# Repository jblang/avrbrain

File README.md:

# AVRBrain

AVRbrain is an [AVR128DB64](https://www.microchip.com/en-us/product/avr128db64) dev board.  The AVR Dx series are modern AVRs with many desireable features over the classic ATmega AVRs, such as multi-voltage I/O, configurable logic, advanced analog features, and a single-wire programming and debug interface.

## Arduino Compatibility

AVRbrain is compatible with the [DxCore](https://github.com/SpenceKonde/DxCore) Arduino Core. I have tested the AVR128DB28 on a breadboard with the same programming circuit I intend to use on the finished board, and confirmed that it works.

Once flashed in UPDI programming mode, the Optiboot_Dx bootloader can be used to reprogram the board in serial comms mode, and there is an auto-reset circuit connected to the DTR line (possible to disable with a jumper).

## PlatformIO Compatibility

AVRbrain is compatible with [PlatformIO](https://platformio.org/) using the [Atmel megaAVR platform](https://docs.platformio.org/en/latest/platforms/atmelmegaavr.html).  PlatformIO supports Arduino development using DxCore, or native development using [avr-libc](https://www.nongnu.org/avr-libc/).  

Here's the `platformio.ini` that I used to build a simple non-Arduino led blinking example for the AVR128DB64:
```
[env:AVR128DB28]
platform = atmelmegaavr
platform_packages = platformio/toolchain-atmelavr@^3.70300.220127
board = AVR128DB28
upload_speed = 115200
upload_flags = 
    --tool
    uart
    --device
    avr128db28
    --uart
    $UPLOAD_PORT
    --clk
    $UPLOAD_SPEED
upload_command = pymcuprog write --erase $UPLOAD_FLAGS --filename $SOURCE
```

The above example can be made to work with DxCore just by adding the line `framework = arduino` to this file.

## Hardware Features
- Onboard CH340C USB-to-serial converter with a micro-USB connector, and a switch to select between USB communication or programming via SerialUPDI.  
- Onboard 3.3V regulator for MVIO. The board is configured to have 3.3V on PORTC and 5V on the other ports.
- SD card holder connected to 3.3V SPI Bus, and an I2C RTC (PCF8563T) with battery backup via CR 1612 coin cell.
- [UEXT port](https://www.olimex.com/Products/Modules/) that exports 3.3V UART, I2C, and SPI buses.  Many peripheral modules are available from Olimex.
- [Qwiic I2C port](https://www.sparkfun.com/qwiic) to work with the Qwiic and Stemma QT ecosystems. Many peripheral modules are available from Sparkfun and Adafruit.
- Headers breaking out all pins of the 8-bit ports A-G, except pin 7 of port F which is UPDI. Pin sockets can be used for stackable shield-style add-on boards, or pin headers can be used to connect to breadboards or elsewhere using IDC cables.
- Port F is used for UPDI, Reset, the USB UART, SD card chip select (level shifted), and optionally the RTC's interrupt and 32 kHz clock signals.
- The RTC's interrupt and 32 kHz clock signals can be connected to port F by adding a solder bridge on the surface mount jumper. The RTC can be disconnected from the I2C bus by cutting the traces in the SDA and SCL jumper pads in case of a conflict with other RTC devices.
- UPDI header for use with a [PicKit](https://www.microchip.com/en-us/development-tool/pg164150) and [MPLAB X](https://www.microchip.com/en-us/tools-resources/develop/mplab-x-ide) for debugging.
- Same size as a Raspberry Pi Model B, though it is not mechanically or electrically compatible. The right-side mounting holes are on the corners instead of toward the middle of the board, and no attempt has been made to reproduce the GPIO header pinout used on the Pi.

## Relationship to z80ctrl NG

[z80ctrl NG](https://github.com/jblang/z80ctrl/tree/master/hardware/nextgen) is the next-generation z80ctrl board I am designing concurrently with AVRbrain.  It uses all the same hardware components, including the AVR128DB64, the USB chip, RTC, voltage regulator, sd card slot, etc.  The primary difference is the pinout. The z80ctrl NG is intended to interface with the [RCBus](https://smallcomputercentral.com/rcbus/) parallel bus used primarily by Z80-based retrocomputers, whereas AVRbrain is intended as a general-purpose dev board with stacking shield-style modules or IDC cables.  z80ctrl also includes a 512K SRAM chip with optional banking that can be initialized by the AVR and then used by the 8-bit processor that z80ctrl shares a bus with.

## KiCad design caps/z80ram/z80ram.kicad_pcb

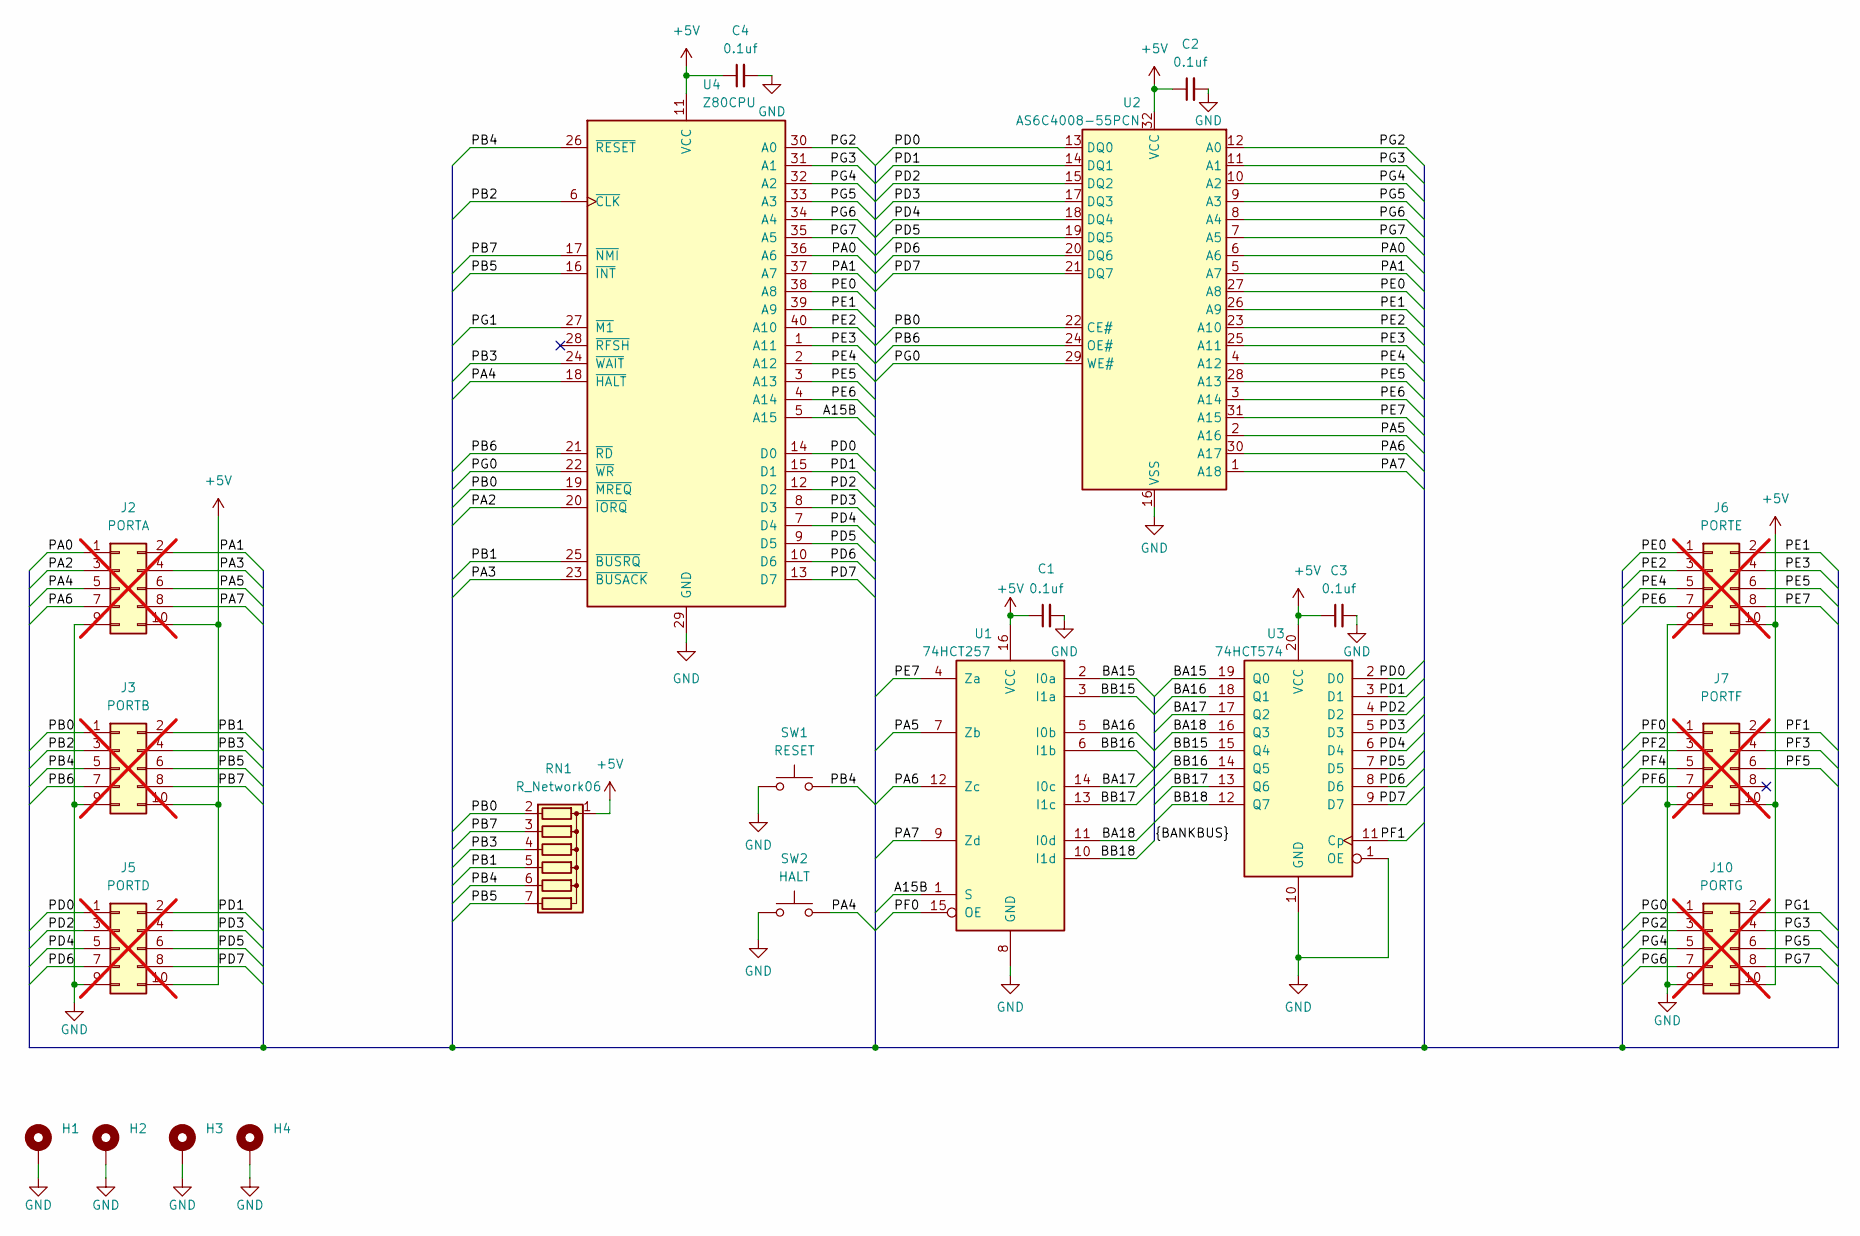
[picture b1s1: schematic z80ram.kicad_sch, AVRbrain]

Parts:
C1, C2, C3, C4: 0.1uf; C_Disc_D3.0mm_W1.6mm_P2.50mm
H1, H2, H3, H4: MountingHole_Pad; MountingHole_2.2mm_M2_Pad_Via
J2: PORTA; PinHeader_2x05_P2.54mm_Vertical; not fitted
J3: PORTB; PinHeader_2x05_P2.54mm_Vertical; not fitted
J5: PORTD; PinHeader_2x05_P2.54mm_Vertical; not fitted
J6: PORTE; PinHeader_2x05_P2.54mm_Vertical; not fitted
J7: PORTF; PinHeader_2x05_P2.54mm_Vertical; not fitted
J10: PORTG; PinHeader_2x05_P2.54mm_Vertical; not fitted
RN1: R_Network06; R_Array_SIP7
SW1: RESET; SW_PUSH_6mm
SW2: HALT; SW_PUSH_6mm
U1: 74HCT257; DIP-16_W7.62mm; MouserPN 595-SN74HCT257N; DigikeyPN 296-8406-5-ND
U2: AS6C4008-55PCN; DIP-32_W15.24mm; MouserPN 913-AS6C4008-55PCN; DigikeyPN 1450-1027-ND
U3: 74HCT574; DIP-20_W7.62mm; MouserPN 595-SN74HCT574N; DigikeyPN 296-1623-5-ND
U4: Z80CPU; DIP-40_W15.24mm

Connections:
+5V: C1.1, C2.1, C3.1, C4.1, J2.10, J3.10, J5.10, J6.10, J7.10, J10.10, RN1.1 (common), U1.16 (VCC), U2.32 (VCC), U3.20 (VCC), U4.11 (VCC)
/A15B: U1.1 (S), U4.5 (A15)
/BA15: U1.2 (I0a), U3.19 (Q0)
/BA16: U1.5 (I0b), U3.18 (Q1)
/BA17: U1.14 (I0c), U3.17 (Q2)
/BA18: U1.11 (I0d), U3.16 (Q3)
/BB15: U1.3 (I1a), U3.15 (Q4)
/BB16: U1.6 (I1b), U3.14 (Q5)
/BB17: U1.13 (I1c), U3.13 (Q6)
/BB18: U1.10 (I1d), U3.12 (Q7)
/PA0: J2.1, U2.6 (A6), U4.36 (A6)
/PA1: J2.2, U2.5 (A7), U4.37 (A7)
/PA2: J2.3, U4.20 (~IORQ)
/PA3: J2.4, U4.23 (~BUSACK)
/PA4: J2.5, SW2.2, U4.18 (~HALT)
/PA5: J2.6, U1.7 (Zb), U2.2 (A16)
/PA6: J2.7, U1.12 (Zc), U2.30 (A17)
/PA7: J2.8, U1.9 (Zd), U2.1 (A18)
/PB0: J3.1, RN1.2 (R1), U2.22 (CE#), U4.19 (~MREQ)
/PB1: J3.2, RN1.5 (R4), U4.25 (~BUSRQ)
/PB2: J3.3, U4.6 (~CLK)
/PB3: J3.4, RN1.4 (R3), U4.24 (~WAIT)
/PB4: J3.5, RN1.6 (R5), SW1.2, U4.26 (~RESET)
/PB5: J3.6, RN1.7 (R6), U4.16 (~INT)
/PB6: J3.7, U2.24 (OE#), U4.21 (~RD)
/PB7: J3.8, RN1.3 (R2), U4.17 (~NMI)
/PD0: J5.1, U2.13 (DQ0), U3.2 (D0), U4.14 (D0)
/PD1: J5.2, U2.14 (DQ1), U3.3 (D1), U4.15 (D1)
/PD2: J5.3, U2.15 (DQ2), U3.4 (D2), U4.12 (D2)
/PD3: J5.4, U2.17 (DQ3), U3.5 (D3), U4.8 (D3)
/PD4: J5.5, U2.18 (DQ4), U3.6 (D4), U4.7 (D4)
/PD5: J5.6, U2.19 (DQ5), U3.7 (D5), U4.9 (D5)
/PD6: J5.7, U2.20 (DQ6), U3.8 (D6), U4.10 (D6)
/PD7: J5.8, U2.21 (DQ7), U3.9 (D7), U4.13 (D7)
/PE0: J6.1, U2.27 (A8), U4.38 (A8)
/PE1: J6.2, U2.26 (A9), U4.39 (A9)
/PE2: J6.3, U2.23 (A10), U4.40 (A10)
/PE3: J6.4, U2.25 (A11), U4.1 (A11)
/PE4: J6.5, U2.4 (A12), U4.2 (A12)
/PE5: J6.6, U2.28 (A13), U4.3 (A13)
/PE6: J6.7, U2.3 (A14), U4.4 (A14)
/PE7: J6.8, U1.4 (Za), U2.31 (A15)
/PF0: J7.1, U1.15 (OE)
/PF1: J7.2, U3.11 (Cp)
/PF2: J7.3
/PF3: J7.4
/PF4: J7.5
/PF5: J7.6
/PF6: J7.7
/PG0: J10.1, U2.29 (WE#), U4.22 (~WR)
/PG1: J10.2, U4.27 (~M1)
/PG2: J10.3, U2.12 (A0), U4.30 (A0)
/PG3: J10.4, U2.11 (A1), U4.31 (A1)
/PG4: J10.5, U2.10 (A2), U4.32 (A2)
/PG5: J10.6, U2.9 (A3), U4.33 (A3)
/PG6: J10.7, U2.8 (A4), U4.34 (A4)
/PG7: J10.8, U2.7 (A5), U4.35 (A5)
GND: C1.2, C2.2, C3.2, C4.2, H1.1, H2.1, H3.1, H4.1, J2.9, J3.9, J5.9, J6.9, J7.9, J10.9, SW1.1, SW2.1, U1.8 (GND), U2.16 (VSS), U3.1 (OE), U3.10 (GND), U4.29 (GND)

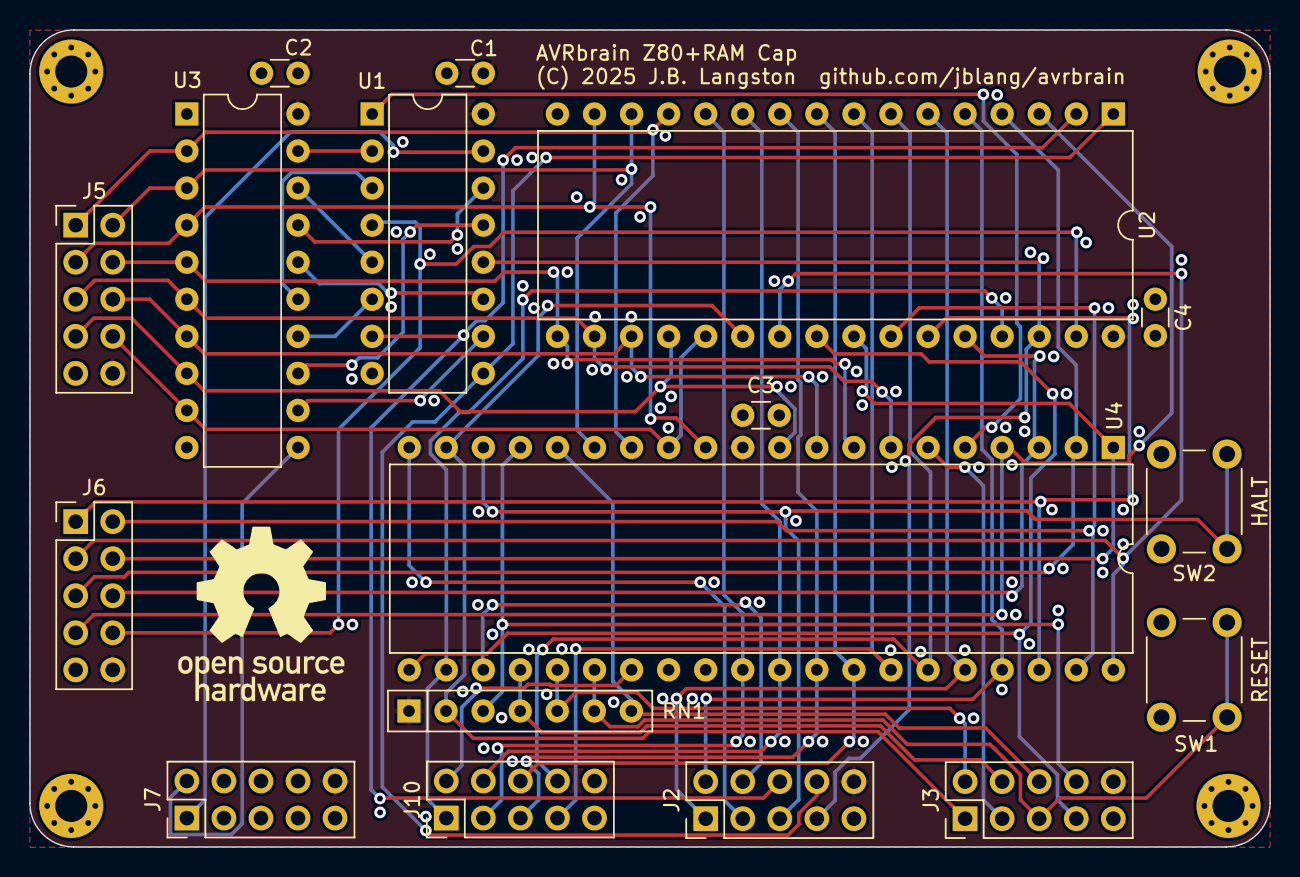
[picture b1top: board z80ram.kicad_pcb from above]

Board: 4 copper layers, 85.0 x 56.0 mm, 21 parts (0 on the bottom side), 53 nets.

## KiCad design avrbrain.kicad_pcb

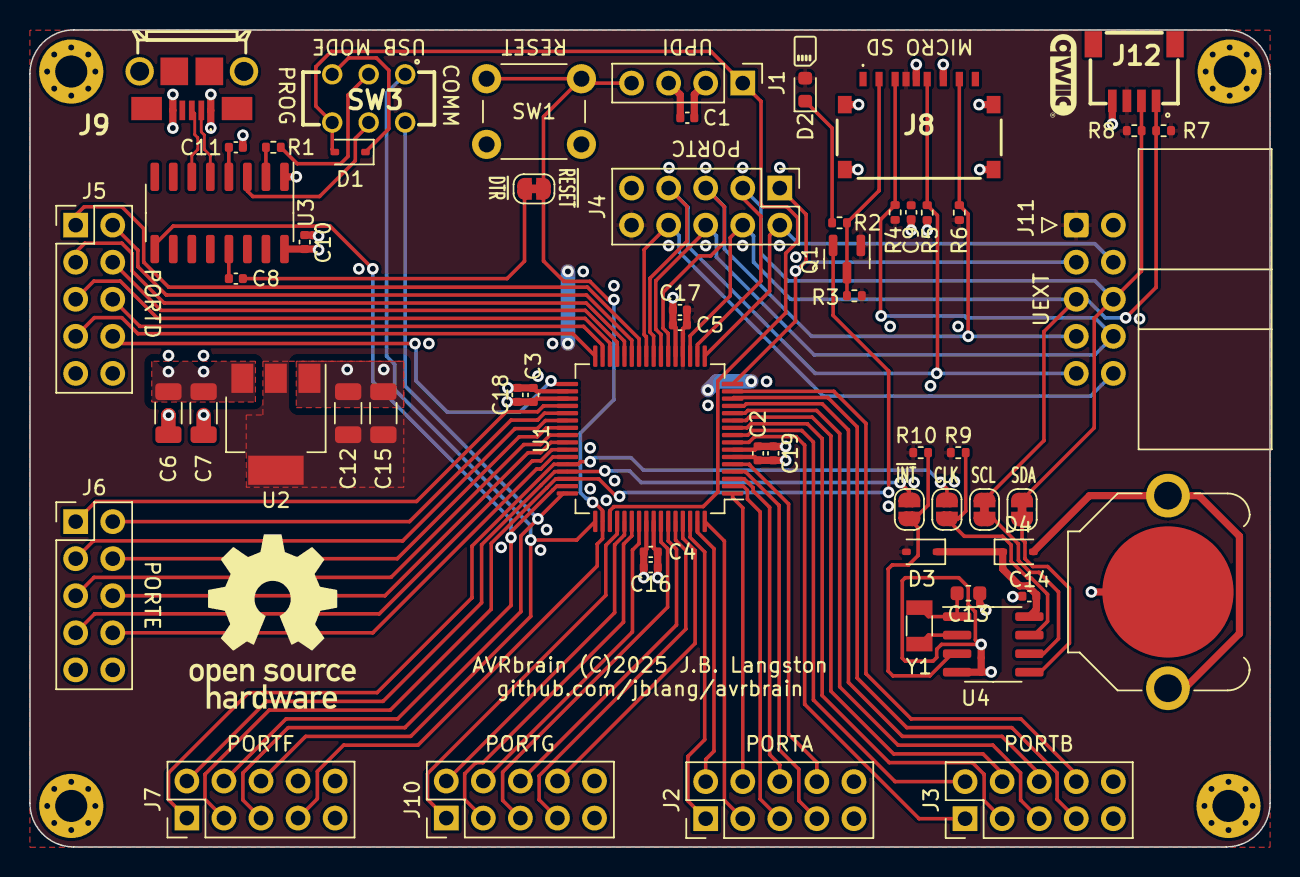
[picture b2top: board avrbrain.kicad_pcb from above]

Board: 4 copper layers, 85.0 x 56.0 mm, 64 parts (0 on the bottom side), 79 nets.

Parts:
BT1: CR1216; BatteryHolder_Keystone_3001_1x12mm
C1, C2, C3, C4, C5, C8, C9, C10, C11, C14: 0.1uf; C_0402_1005Metric
C6, C15: 22uf; C_1206_3216Metric
C7, C12: 1uf; C_1206_3216Metric
C13: 27pf; C_0603_1608Metric
C16, C17, C18, C19: 1uf; C_0402_1005Metric
D1, D3, D4: 1N5819WS; D_SOD-323
D2: LED; LED_0603_1608Metric
H1, H2, H3, H4: MountingHole_Pad; MountingHole_2.2mm_M2_Pad_Via
J1: UPDI; PinHeader_1x04_P2.54mm_Vertical
J2: PORTA; PinHeader_2x05_P2.54mm_Vertical
J3: PORTB; PinHeader_2x05_P2.54mm_Vertical
J4: PORTC; PinHeader_2x05_P2.54mm_Vertical
J5: PORTD; PinHeader_2x05_P2.54mm_Vertical
J6: PORTE; PinHeader_2x05_P2.54mm_Vertical
J7: PORTF; PinHeader_2x05_P2.54mm_Vertical
J8: XKTF-0803-0; XKTF08030
J9: U254-051T-4BH81-S2S; U254051T4BH81S2S
J10: PORTG; PinHeader_2x05_P2.54mm_Vertical
J11: UEXT; IDC-Header_2x05_P2.54mm_Horizontal
J12: SM04B-SRSS-TB; SM04B-SRSS-TB_LFSN_
JP1: AUTORESET; SolderJumper-2_P1.3mm_Bridged_RoundedPad1.0x1.5mm
JP2: RTC_SCL; SolderJumper-2_P1.3mm_Bridged_RoundedPad1.0x1.5mm
JP3: RTC_SDA; SolderJumper-2_P1.3mm_Bridged_RoundedPad1.0x1.5mm
JP6: RTC_CLK; SolderJumper-2_P1.3mm_Open_RoundedPad1.0x1.5mm
JP7: RTC_INT; SolderJumper-2_P1.3mm_Open_RoundedPad1.0x1.5mm
NT1: NetTie_2; NetTie-2_SMD_Pad0.5mm
Q1: BSS138; SOT-23
R1, R2: 1K; R_0402_1005Metric
R3, R4, R5, R6: 100K; R_0402_1005Metric
R7, R8, R9, R10: 2.2K; R_0402_1005Metric
SW1: RESET; SW_PUSH_6mm
SW3: PROG_EN; JS202011CQN
U1: AVR128DB64x-xPT; TQFP-64_10x10mm_P0.5mm
U2: AMS1117-3.3; SOT-223-3_TabPin2
U3: CH340C; SOIC-16_3.9x9.9mm_P1.27mm
U4: PCF8563T; SOIC-8_3.9x4.9mm_P1.27mm
Y1: 32kHz; Crystal_SMD_3215-2Pin_3.2x1.5mm

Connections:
+3.3V: C5.1, C9.1, C12.1, C15.1, C17.2, D2.2 (A), D3.2 (A), J4.10, J8.P4 (VDD), J11.1, J12.3, Q1.1 (G), R3.1, R4.1, R6.1, R7.1, R8.1, R9.1, R10.1, U1.20 (VDDIO2), U2.2 (VO)
+5V: C1.1, C2.2, C3.2, C4.1, C6.1, C7.1, C10.1, C16.2, C18.2, C19.2, J1.2, J2.10, J3.10, J5.10, J6.10, J7.10, J9.1 (VBUS), J10.10, U1.6 (VDD), U1.34 (AVDD), U1.56 (VDD), U2.3 (VI), U3.16 (VCC)
/PA0: J2.1, U1.62 (XTALHF1/PA0)
/PA1: J2.2, U1.63 (XTALHF2/PA1)
/PA2: J2.3, U1.64 (PA2)
/PA3: J2.4, U1.1 (PA3)
/PA4: J2.5, U1.2 (PA4)
/PA5: J2.6, U1.3 (PA5)
/PA6: J2.7, U1.4 (PA6)
/PA7: J2.8, U1.5 (PA7)
/PB0: J3.1, U1.8 (PB0)
/PB1: J3.2, U1.9 (PB1)
/PB2: J3.3, U1.10 (PB2)
/PB3: J3.4, U1.11 (PB3)
/PB4: J3.5, U1.12 (PB4)
/PB5: J3.6, U1.13 (PB5)
/PB6: J3.7, U1.14 (PB6)
/PB7: J3.8, U1.15 (PB7)
/PD0: J5.1, U1.26 (PD0)
/PD1: J5.2, U1.27 (PD1)
/PD2: J5.3, U1.28 (PD2)
/PD3: J5.4, U1.29 (PD3)
/PD4: J5.5, U1.30 (PD4)
/PD5: J5.6, U1.31 (PD5)
/PD6: J5.7, U1.32 (PD6)
/PD7: J5.8, U1.33 (VREFA/PD7)
/PE0: J6.1, U1.36 (PE0)
/PE1: J6.2, U1.37 (PE1)
/PE2: J6.3, U1.38 (PE2)
/PE3: J6.4, U1.39 (PE3)
/PE4: J6.5, U1.40 (PE4)
/PE5: J6.6, U1.41 (PE5)
/PE6: J6.7, U1.42 (PE6)
/PE7: J6.8, U1.43 (PE7)
/PG0: J10.1, U1.52 (PG0)
/PG1: J10.2, U1.53 (PG1)
/PG2: J10.3, U1.54 (PG2)
/PG3: J10.4, U1.55 (PG3)
/PG4: J10.5, U1.58 (PG4)
/PG5: J10.6, U1.59 (PG5)
/PG6: J10.7, U1.60 (PG6)
/PG7: J10.8, U1.61 (PG7)
/Peripherals/UD+: J9.3 (D+), U3.6 (UD-)
/Peripherals/UD-: J9.2 (D-), U3.5 (UD+)
/Peripherals/USBRX: SW3.5 (B), U3.3 (RXD)
/Peripherals/USBTX: R1.2, SW3.2 (B)
CLK32K: J7.1, JP6.1 (A), U1.44 (XTAL32K1/PF0)
GND: BT1.2 (-), C1.2, C2.1, C3.1, C4.2, C5.2, C6.2, C7.2, C9.2, C10.2, C11.2, C12.2, C14.2, C15.2, C16.1, C17.1, C18.1, C19.1, H1.1, H2.1, H3.1, H4.1, J1.3, J2.9, J3.9, J4.9, J5.9, J6.9, J7.9, J8.G1 (DET), J8.MP1, J8.MP2, J8.MP3, J8.MP4, J8.P6 (VSS), J9.5 (GND), J10.9, J11.2, J12.4, NT1.2, R5.1, SW1.1, U1.7 (GND), U1.21 (GND), U1.35 (AGND), U1.57 (GND), U2.1 (GND), U3.1 (GND), U4.4 (VSS)
GND1: C13.1, NT1.1
MISO: J4.5, J8.P7 (DAT0), J11.7, R6.2, U1.22 (PC4)
MOSI: J4.6, J8.P3 (CMD), J11.8, R4.2, U1.23 (PC5)
unnamed: BT1.1 (+), D4.2 (A)
unnamed: D1.1 (K), SW3.3 (C)
unnamed: D2.1 (K), R2.2
unnamed: C14.1, D3.1 (K), D4.1 (K), U4.8 (VDD)
unnamed: J8.P2 (DAT3/CD), Q1.3 (D), R2.1, R3.2
unnamed: C8.2, JP1.1 (A)
unnamed: JP2.2 (B), U4.6 (SCL)
unnamed: JP3.2 (B), U4.5 (SDA)
unnamed: JP6.2 (B), R9.2, U4.7 (CLKO)
unnamed: JP7.2 (B), R10.2, U4.3 (~INT)
unnamed: R1.1, U3.2 (TXD)
unnamed: C11.1, U3.4 (V3)
unnamed: C8.1, U3.13 (~DTR)
unnamed: C13.2, U4.1 (OSCI), Y1.2
unnamed: U4.2 (OSCO), Y1.1
RXC: J4.2, J11.4, U1.17 (PC1)
RXF: J7.6, SW3.1 (A), U1.49 (PF5)
SCK: J4.7, J8.P5 (CLK), J11.9, R5.2, U1.24 (PC6)
SCL: J4.4, J11.5, J12.1, JP2.1 (A), R7.2, U1.19 (PC3)
SDA: J4.3, J11.6, J12.2, JP3.1 (A), R8.2, U1.18 (PC2)
TXC: J4.1, J11.3, U1.16 (PC0)
TXF: J7.5, SW3.4 (A), U1.48 (PF4)
UPDI: D1.2 (A), J1.1, SW3.6 (C), U1.51 (UPDI)
~CS: J4.8, J11.10, U1.25 (PC7)
~CTS: J7.4, U1.47 (PF3), U3.9 (~CTS)
~RESET: J1.4, J7.7, JP1.2 (B), SW1.2, U1.50 (~RESET/PF6)
~RTCINT: J7.2, JP7.1 (A), U1.45 (XTAL32K2/PF1)
~SDCS: J7.3, Q1.2 (S), U1.46 (PF2)

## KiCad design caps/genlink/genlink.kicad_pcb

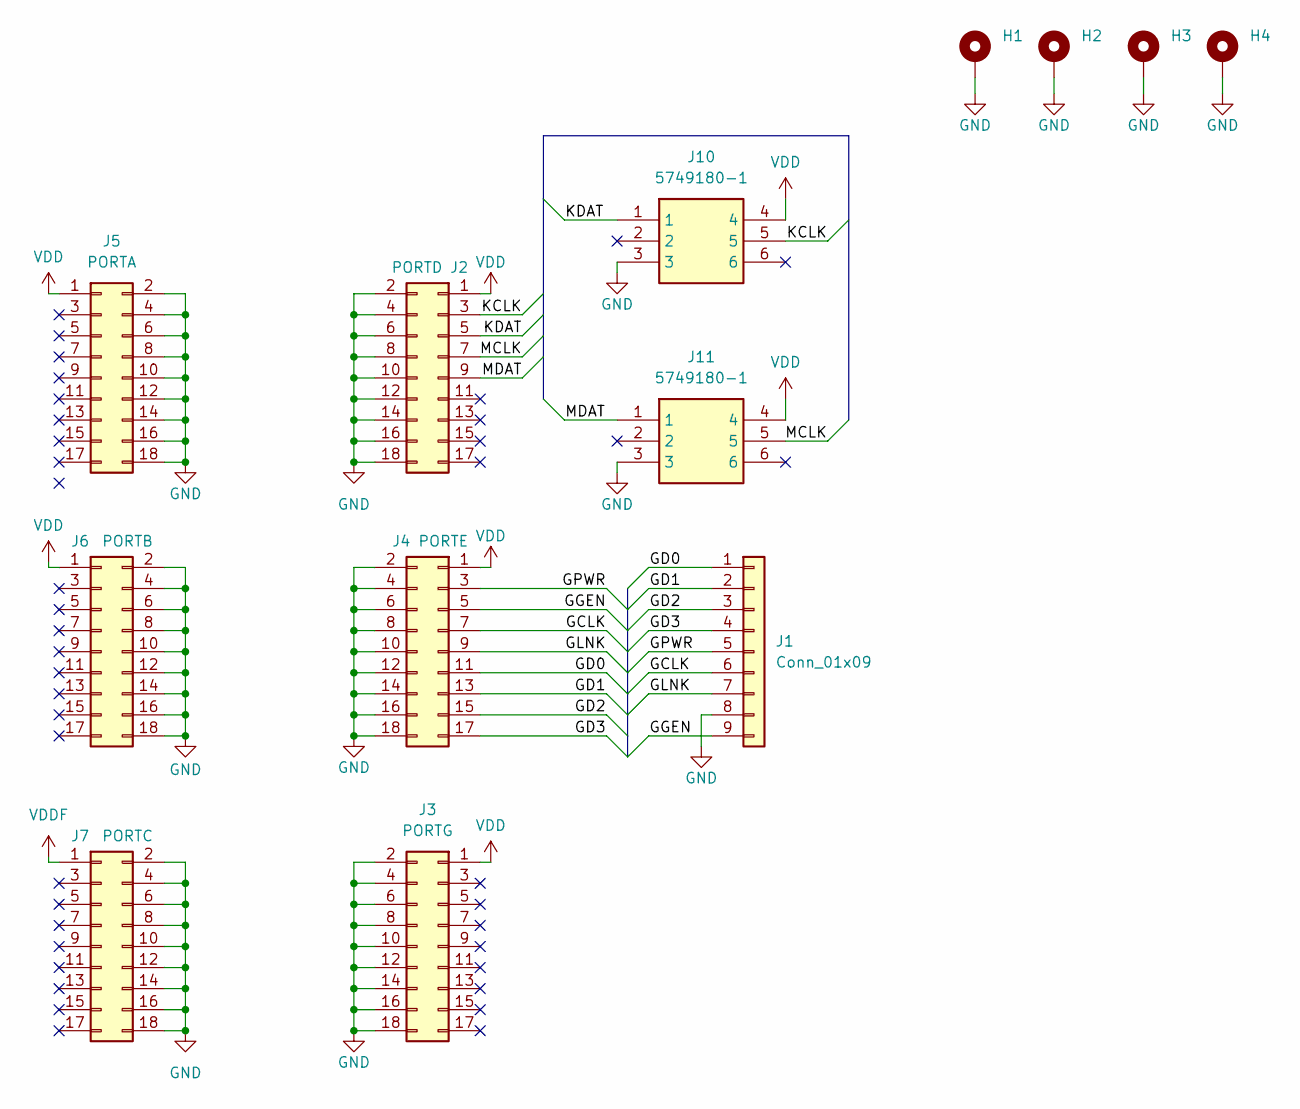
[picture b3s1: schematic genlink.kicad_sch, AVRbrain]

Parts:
H1, H2, H3, H4: MountingHole_Pad; MountingHole_2.2mm_M2_Pad_Via
J1: Conn_01x09; 182-009-213R561
J2: PORTD; PinSocket_2x09_P2.54mm_Vertical
J3: PORTG; PinSocket_2x09_P2.54mm_Vertical
J4: PORTE; PinSocket_2x09_P2.54mm_Vertical
J5: PORTA; PinSocket_2x09_P2.54mm_Vertical
J6: PORTB; PinSocket_2x09_P2.54mm_Vertical
J7: PORTC; PinSocket_2x09_P2.54mm_Vertical
J10, J11: 5749180-1; Mouser Part Number 571-5749180-1

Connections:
/GCLK: J1.6, J4.7
/GD0: J1.1, J4.11
/GD1: J1.2, J4.13
/GD2: J1.3, J4.15
/GD3: J1.4, J4.17
/GGEN: J1.9, J4.5
/GLNK: J1.7, J4.9
/GPWR: J1.5, J4.3
/KCLK: J2.3, J10.5
/KDAT: J2.5, J10.1
/MCLK: J2.7, J11.5
/MDAT: J2.9, J11.1
GND: H1.1, H2.1, H3.1, H4.1, J1.8, J2.2, J2.4, J2.6, J2.8, J2.10, J2.12, J2.14, J2.16, J2.18, J3.2, J3.4, J3.6, J3.8, J3.10, J3.12, J3.14, J3.16, J3.18, J4.2, J4.4, J4.6, J4.8, J4.10, J4.12, J4.14, J4.16, J4.18, J5.2, J5.4, J5.6, J5.8, J5.10, J5.12, J5.14, J5.16, J5.18, J6.2, J6.4, J6.6, J6.8, J6.10, J6.12, J6.14, J6.16, J6.18, J7.2, J7.4, J7.6, J7.8, J7.10, J7.12, J7.14, J7.16, J7.18, J10.3, J11.3
VDD: J2.1, J3.1, J4.1, J5.1, J6.1, J10.4, J11.4
VDDF: J7.1

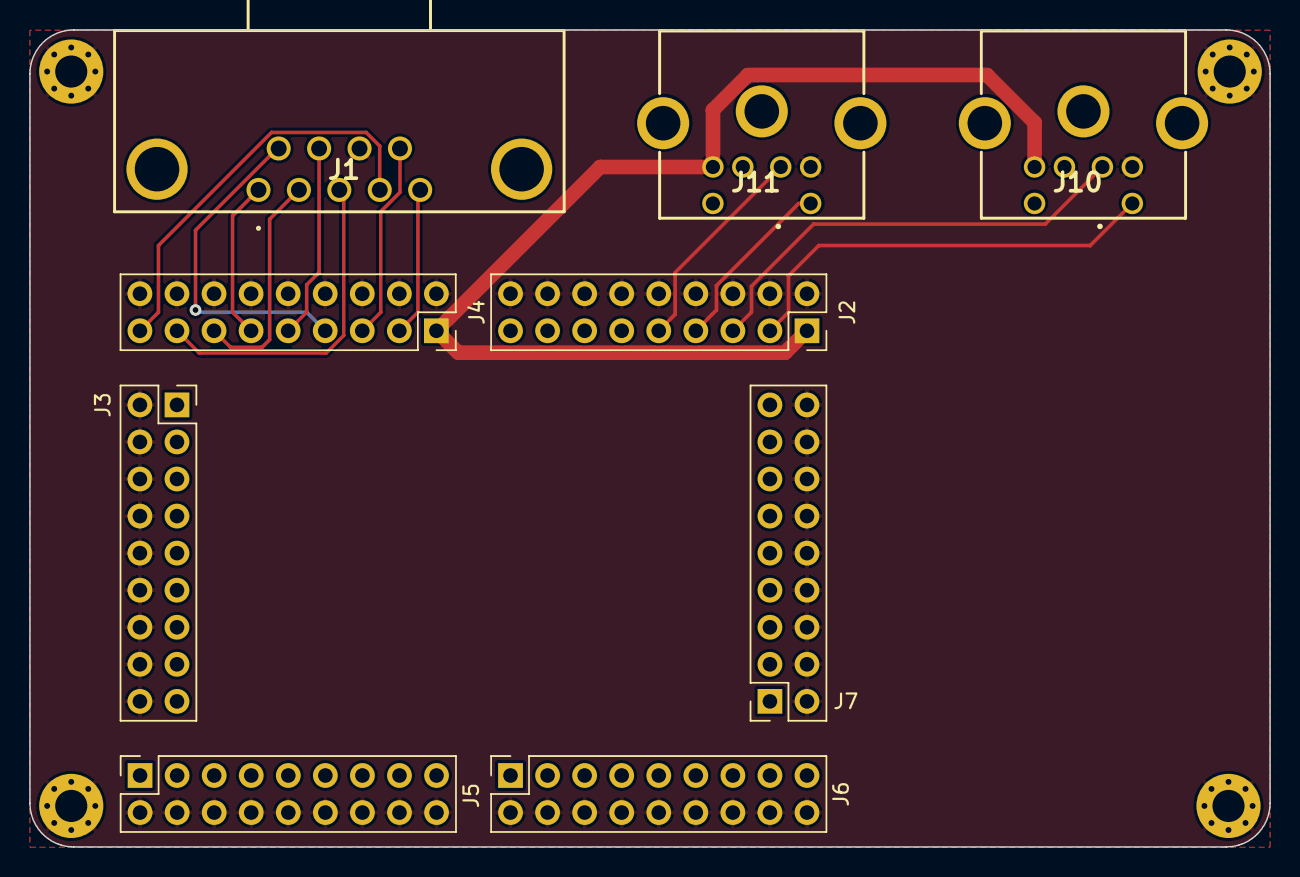
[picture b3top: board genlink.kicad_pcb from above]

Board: 2 copper layers, 85.0 x 56.0 mm, 13 parts (0 on the bottom side), 14 nets.

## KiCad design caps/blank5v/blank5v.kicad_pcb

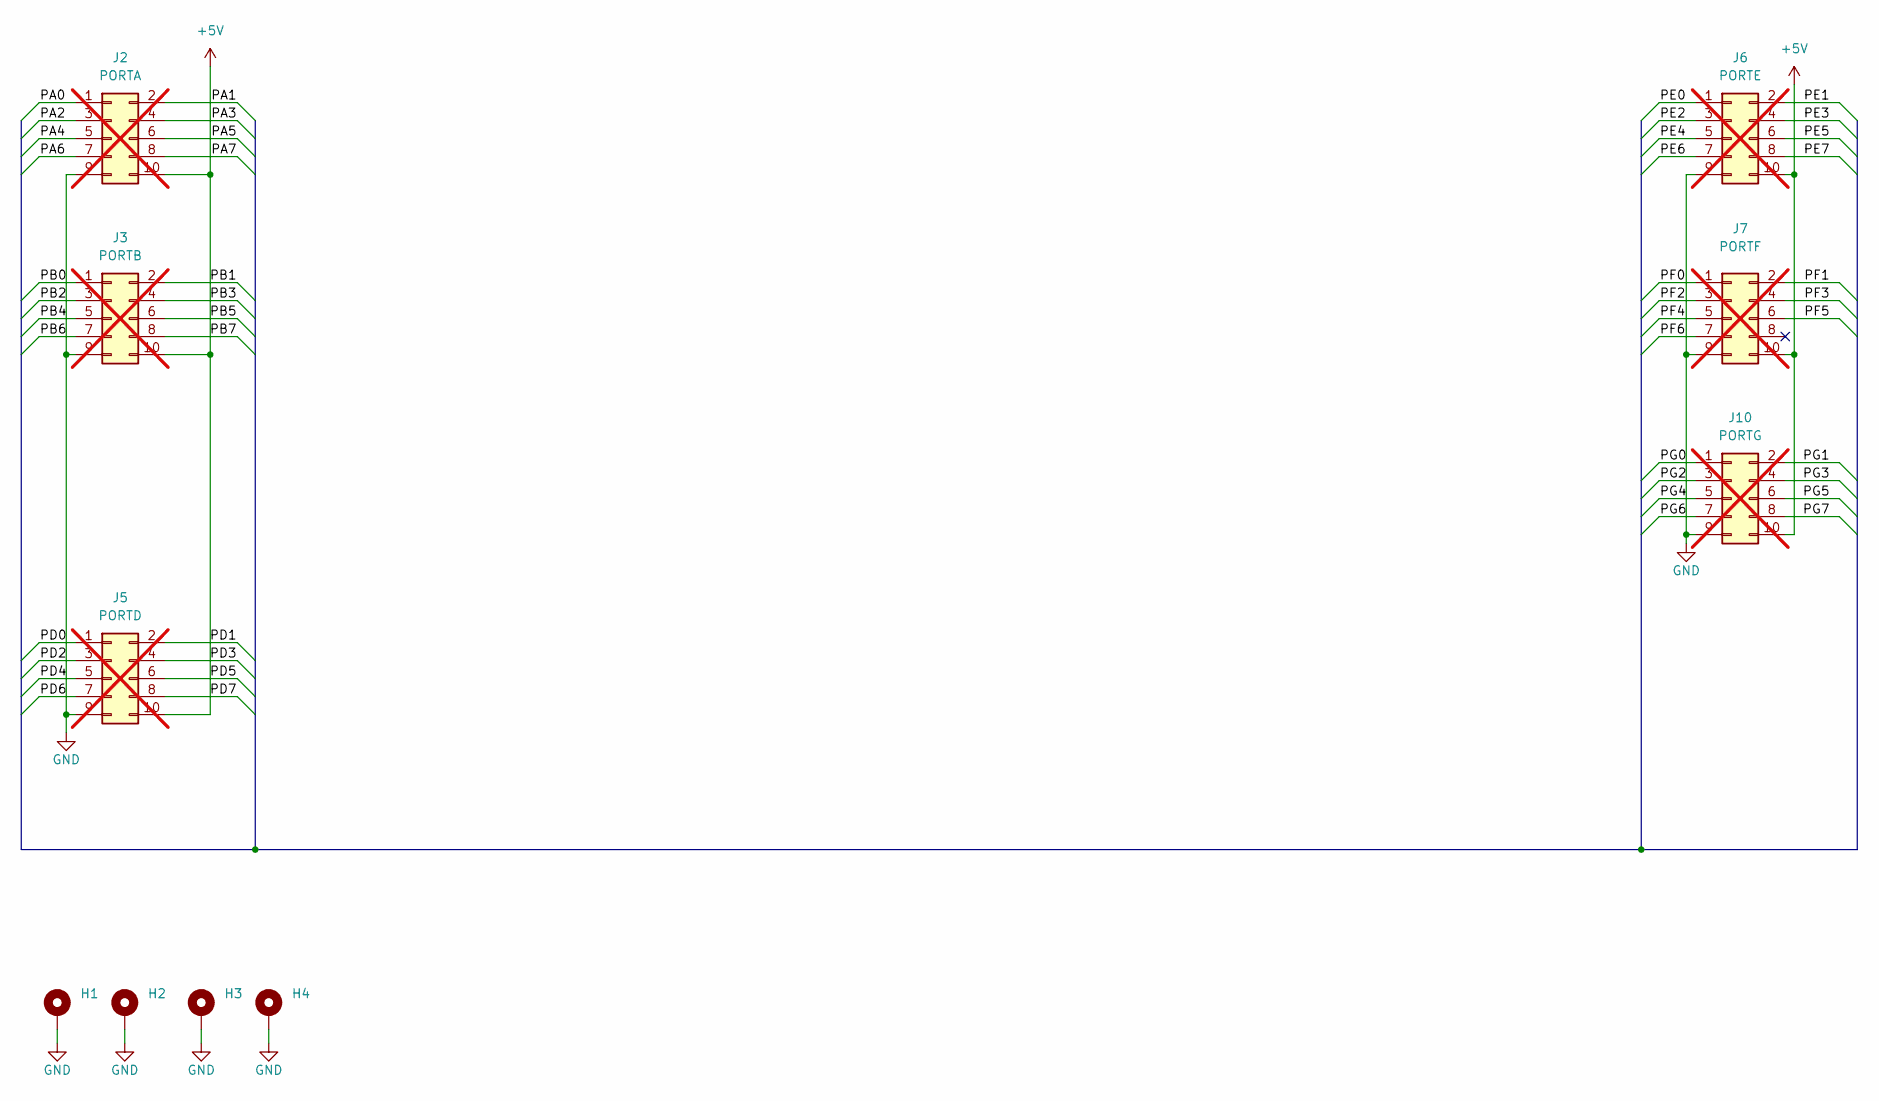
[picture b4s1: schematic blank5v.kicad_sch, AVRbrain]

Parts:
H1, H2, H3, H4: MountingHole_Pad; MountingHole_2.2mm_M2_Pad_Via
J2: PORTA; PinHeader_2x05_P2.54mm_Vertical; not fitted
J3: PORTB; PinHeader_2x05_P2.54mm_Vertical; not fitted
J5: PORTD; PinHeader_2x05_P2.54mm_Vertical; not fitted
J6: PORTE; PinHeader_2x05_P2.54mm_Vertical; not fitted
J7: PORTF; PinHeader_2x05_P2.54mm_Vertical; not fitted
J10: PORTG; PinHeader_2x05_P2.54mm_Vertical; not fitted

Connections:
+5V: J2.10, J3.10, J5.10, J6.10, J7.10, J10.10
/PA0: J2.1
/PA1: J2.2
/PA2: J2.3
/PA3: J2.4
/PA4: J2.5
/PA5: J2.6
/PA6: J2.7
/PA7: J2.8
/PB0: J3.1
/PB1: J3.2
/PB2: J3.3
/PB3: J3.4
/PB4: J3.5
/PB5: J3.6
/PB6: J3.7
/PB7: J3.8
/PD0: J5.1
/PD1: J5.2
/PD2: J5.3
/PD3: J5.4
/PD4: J5.5
/PD5: J5.6
/PD6: J5.7
/PD7: J5.8
/PE0: J6.1
/PE1: J6.2
/PE2: J6.3
/PE3: J6.4
/PE4: J6.5
/PE5: J6.6
/PE6: J6.7
/PE7: J6.8
/PF0: J7.1
/PF1: J7.2
/PF2: J7.3
/PF3: J7.4
/PF4: J7.5
/PF5: J7.6
/PF6: J7.7
/PG0: J10.1
/PG1: J10.2
/PG2: J10.3
/PG3: J10.4
/PG4: J10.5
/PG5: J10.6
/PG6: J10.7
/PG7: J10.8
GND: H1.1, H2.1, H3.1, H4.1, J2.9, J3.9, J5.9, J6.9, J7.9, J10.9

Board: 4 copper layers, 10 parts (0 on the bottom side), 2 nets, no tracks yet.

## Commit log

2024-01-10 Initial layout of new AVR128DB64 dev board
2024-01-15 Tweaks to layout, finish all connections
2024-01-24 Finish layout and routing
2024-01-25 Put resistor before switch to avoid parasitic powering of the board
2024-01-26 Add README and update 3D render
2024-03-30 Final touches
2025-01-18 Switch to 4 layer; reduce connector size and move to edge
2025-01-18 Add blank template with 5V connectors
2025-01-18 Add Z80+RAM cap
2025-01-20 OCD tweaks
2025-01-20 Add silkscreen pinouts
2025-01-20 Final (?!) tweaks
2025-01-20 Add reset and halt buttons to Z80 cap
2025-01-20 Add custom symbols and footprints
2025-01-20 Add LCSC part numbers
2025-01-20 Fix LCSC field name, gerber settings
2025-01-20 Final tweaks after uploading to JLC
2025-01-20 Generate gerbers for Z80+RAM cap

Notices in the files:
avrbrain.kicad_pcb:
AVRbrain (C)2025 J.B. Langston
caps/blank5v/blank5v.kicad_sch:
(C) 2023 J.B. Langston
caps/z80ram/z80ram.kicad_pcb:
(C) 2025 J.B. Langston  github.com/jblang/avrbrain
